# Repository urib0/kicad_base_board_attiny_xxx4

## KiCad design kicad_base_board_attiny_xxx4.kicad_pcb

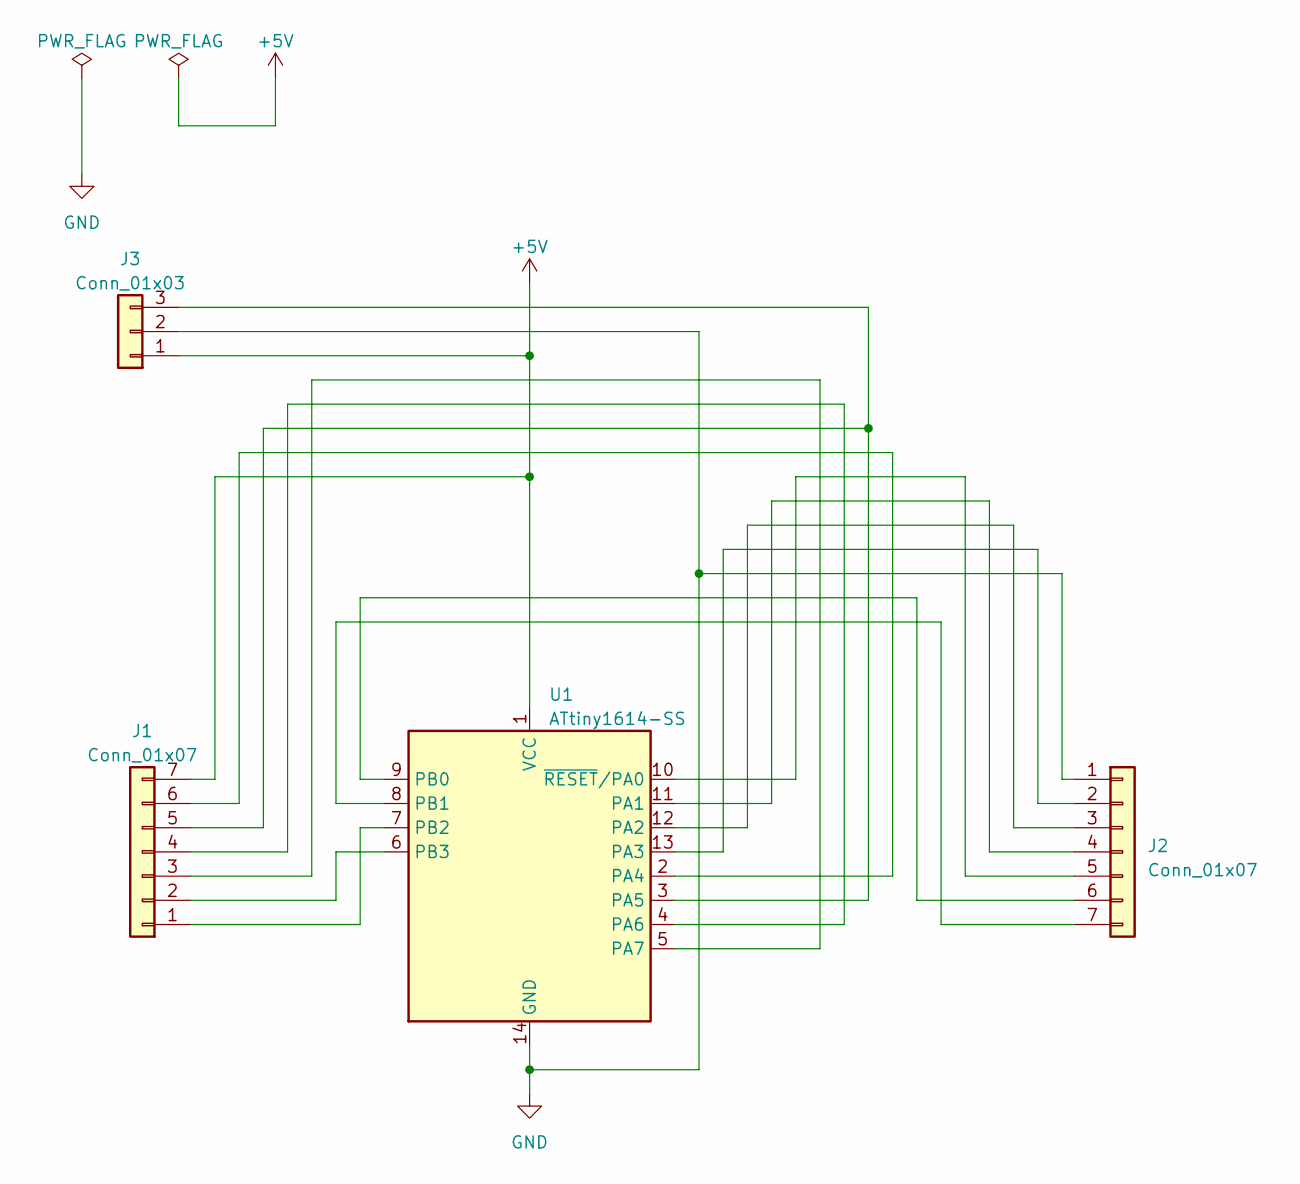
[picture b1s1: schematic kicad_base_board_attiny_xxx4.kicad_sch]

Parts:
J1, J2: Conn_01x07; PinHeader_1x07_P1.27mm_Vertical
J3: Conn_01x03; PinHeader_1x03_P1.27mm_Vertical
U1: ATtiny1614-SS; SOIC-14_3.9x8.7mm_P1.27mm

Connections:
+5V: J1.7, J3.1, U1.1 (VCC)
GND: J2.1, J3.2, U1.14 (GND)
unnamed: J1.1, U1.7 (PB2)
unnamed: J1.2, U1.6 (PB3)
unnamed: J1.3, U1.5 (PA7)
unnamed: J1.4, U1.4 (PA6)
unnamed: J1.5, J3.3, U1.3 (PA5)
unnamed: J1.6, U1.2 (PA4)
unnamed: J2.2, U1.13 (PA3)
unnamed: J2.3, U1.12 (PA2)
unnamed: J2.4, U1.11 (PA1)
unnamed: J2.5, U1.10 (~RESET/PA0)
unnamed: J2.6, U1.9 (PB0)
unnamed: J2.7, U1.8 (PB1)

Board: 2 copper layers, 4 parts (0 on the bottom side), 14 nets, no tracks yet.
